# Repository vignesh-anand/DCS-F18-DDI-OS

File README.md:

# Open Source F18 DDI for DCS

Quick project to build a functional Digital Display Indicator for the F18 Hornet in DCS World. The project is not meant to be a replica of the real device but act as a completely functional module to enhance the immersion and combat experience. This might also be good for other modules like the F16 but this is untested Here's a demo:

[https://youtu.be/Hzj8HVoCLto](https://youtu.be/Hzj8HVoCLto)

### Bill of Materials

| Item Name | Price | Quantity | Purchase Link | Notes |
| --- | --- | --- | --- | --- |
| Custom PCB | $32 for 5 | 1 | [https://jlcpcb.com/](https://jlcpcb.com/) | Gerber files available in the repository, can order from any online PCB manufacturer. I like JLCPCB |
| Panasonic ESE-20D443 Switches | $1.18 | 20 | [https://www.digikey.com/en/products/detail/panasonic-electronic-components/ESE-20D443/593515](https://www.digikey.com/en/products/detail/panasonic-electronic-components/ESE-20D443/593515) | Available on Digikey or Mouser |
| Waveshare 4inch HDMI Capacitive Touch IPS LCD | $66 | 1 | [https://www.waveshare.com/4inch-hdmi-lcd-c.htm](https://www.waveshare.com/4inch-hdmi-lcd-c.htm) | Quicker shipping on Amazon but more expensive |
| Seed Studio Xiao Samd21 | $5.4 | 1 | [https://www.seeedstudio.com/Seeeduino-XIAO-Arduino-Microcontroller-SAMD21-Cortex-M0+-p-4426.html?srsltid=AfmBOoq5dJ23LE_dqcqwzZtpAwAl_5tHTdahaePdUQaOJm6XNmBkNnsp](https://www.seeedstudio.com/Seeeduino-XIAO-Arduino-Microcontroller-SAMD21-Cortex-M0+-p-4426.html?srsltid=AfmBOoq5dJ23LE_dqcqwzZtpAwAl_5tHTdahaePdUQaOJm6XNmBkNnsp) |  |
| M3 Bolts | $7.99 | 1 | [https://a.co/d/crp1qAX](https://a.co/d/crp1qAX) |  |
| M2.5 Bolts | $7.57 | 1 | [https://a.co/d/fGeQGS1](https://a.co/d/fGeQGS1) |  |

Total: $142 for one, $108 each for three

### Assembling the Module

**Step 1:** Solder header pins of the Seed Studio Xiao to the PCB and then solder on the board itself. A small dot on the PCB marks pin 1 of the board

**Step 2:** Solder the 20 push switches on the PCB

**Step 3:** Flash the Xiao board (see below)

**Step 4:** Mount the Display into the backplate using the M2.5 bolts

**Step 5:** Place the PCB in the backplate, place the front plate on it, and then secure all three using the M3 bolts

### Flashing the Microcontroller on Arduino IDE

**Step 1:** Download Arduino IDE - [https://www.arduino.cc/en/software/](https://www.arduino.cc/en/software/)

**Step 2:** Open the attached sketch in the IDE

**Step 3:** Add Seed studio board to the IDE - [https://wiki.seeedstudio.com/Seeed_Arduino_Boards/](https://wiki.seeedstudio.com/Seeed_Arduino_Boards/)

**Step 4:** In the library manager install the **HID-Project** library by NicoHood

**Step 5:** Set the Xiao to bootloader mode

**Step 6:** Under Tools → USB Stack, choose Arduino or Native

**Step 7:** Hit upload

**Step 8:** Disconnect and reconnect the microcontroller for it to appear as a joystick/controller

**Note:** If it does not appear as a joystick, find the device in device manager, and uninstall driver, then reconnect the device.

### Configuring DCS

**Exporting Displays:**

Exporting specific displays can be achieved via creating lua files: [https://wiki.hoggitworld.com/view/Exporting_MFCD_Displays](https://wiki.hoggitworld.com/view/Exporting_MFCD_Displays). Sample Lua for this DDI is attached to the repo. First set up your displays in windows as the following before continuing. Adjust the resolution in the lua file to match your resolution.

**Button Mappings:**

The DDI will detect like a regular gamepad/controller with 20 buttons. In the F18 DCS module, button one of the DDI is the bottom most button of the left bank. Choose the command in DCS then click the appropriate button on the module to map.

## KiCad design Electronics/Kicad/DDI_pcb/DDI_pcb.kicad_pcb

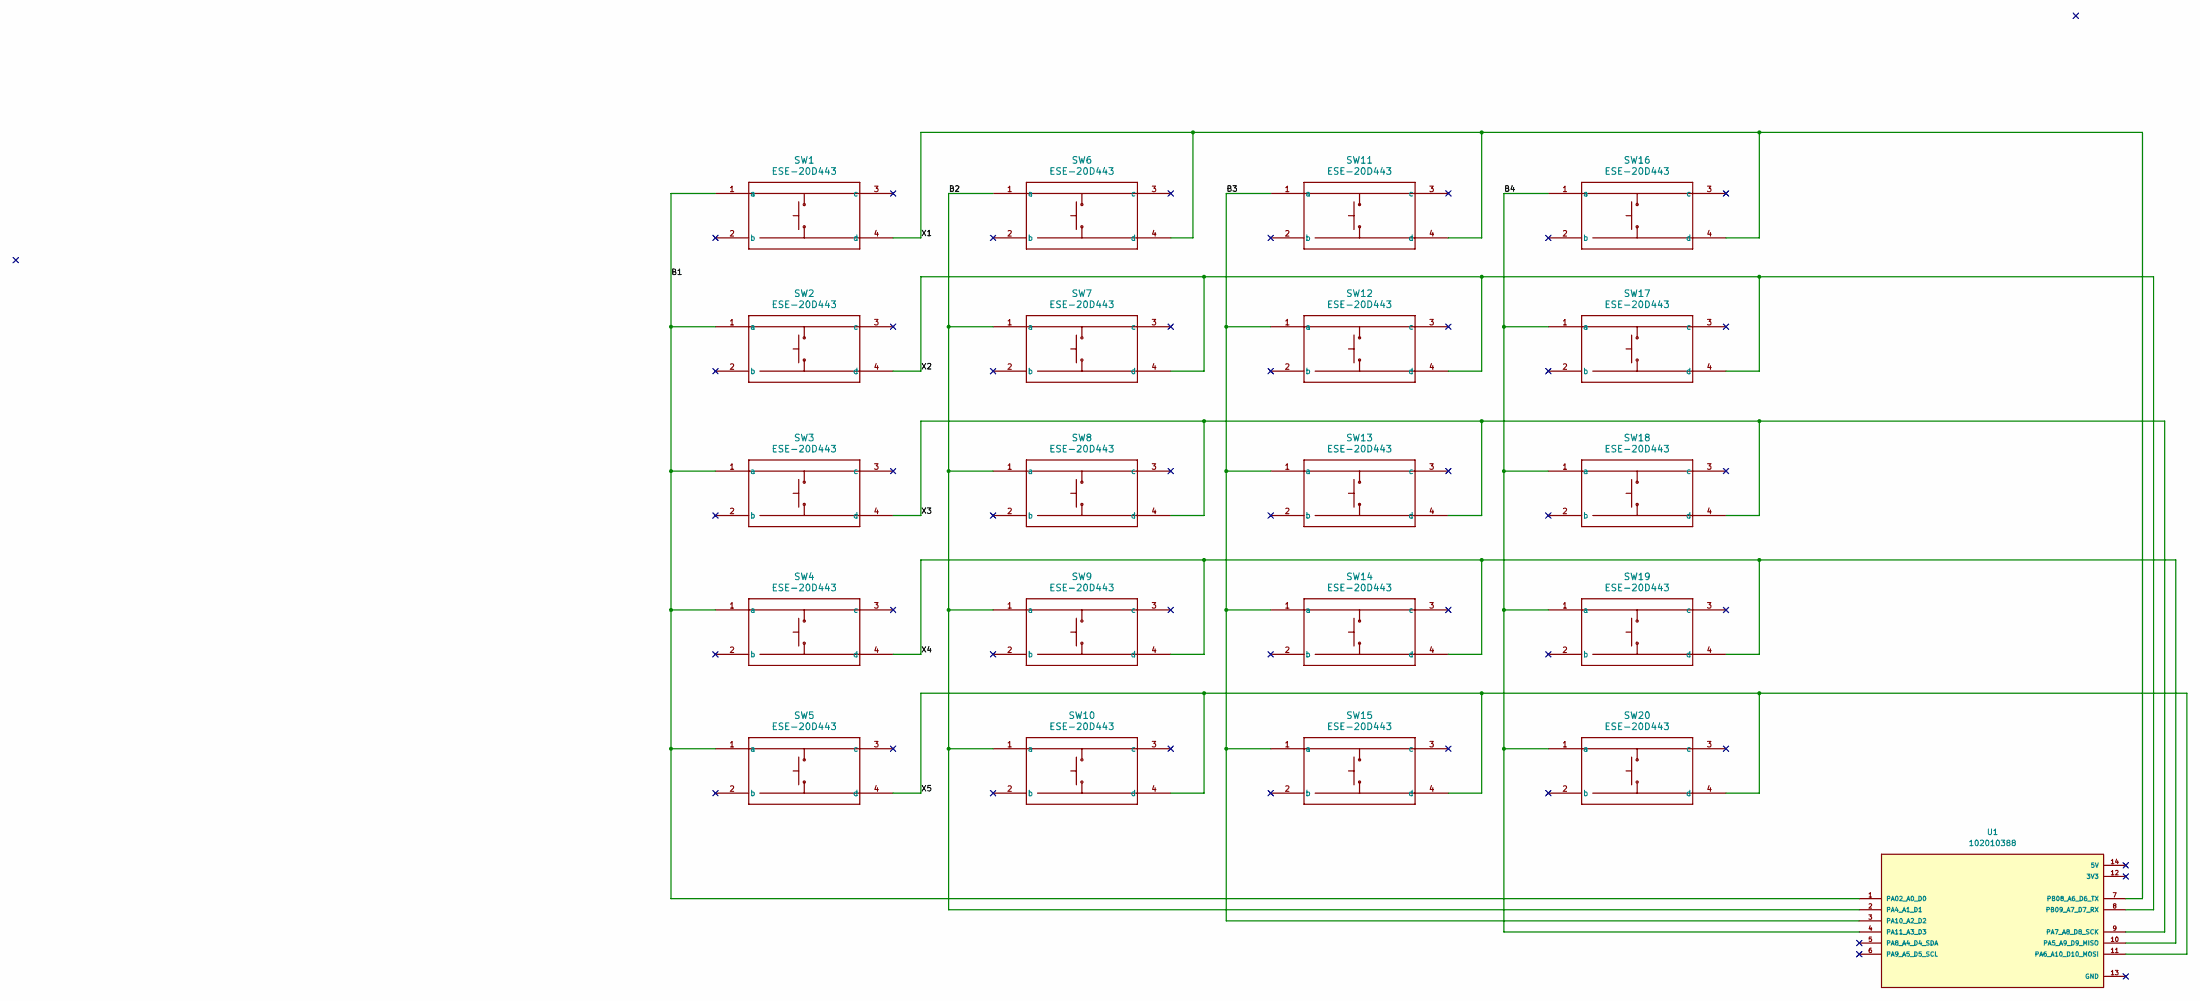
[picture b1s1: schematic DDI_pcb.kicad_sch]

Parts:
SW1, SW2, SW3, SW4, SW5, SW6, SW7, SW8, SW9, SW10, SW11, SW12, SW13, SW14, SW15, SW16, SW17, SW18, SW19, SW20: ESE-20D443; SW4_ESE-20D443_PAN
U1: 102010388; MODULE_113991054; PARTREV N/A

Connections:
/B1: SW1.1 (a), SW2.1 (a), SW3.1 (a), SW4.1 (a), SW5.1 (a), U1.1 (PA02_A0_D0)
/B2: SW6.1 (a), SW7.1 (a), SW8.1 (a), SW9.1 (a), SW10.1 (a), U1.2 (PA4_A1_D1)
/B3: SW11.1 (a), SW12.1 (a), SW13.1 (a), SW14.1 (a), SW15.1 (a), U1.3 (PA10_A2_D2)
/B4: SW16.1 (a), SW17.1 (a), SW18.1 (a), SW19.1 (a), SW20.1 (a), U1.4 (PA11_A3_D3)
/X1: SW1.4 (d), SW6.4 (d), SW11.4 (d), SW16.4 (d), U1.7 (PB08_A6_D6_TX)
/X2: SW2.4 (d), SW7.4 (d), SW12.4 (d), SW17.4 (d), U1.8 (PB09_A7_D7_RX)
/X3: SW3.4 (d), SW8.4 (d), SW13.4 (d), SW18.4 (d), U1.9 (PA7_A8_D8_SCK)
/X4: SW4.4 (d), SW9.4 (d), SW14.4 (d), SW19.4 (d), U1.10 (PA5_A9_D9_MISO)
/X5: SW5.4 (d), SW10.4 (d), SW15.4 (d), SW20.4 (d), U1.11 (PA6_A10_D10_MOSI)

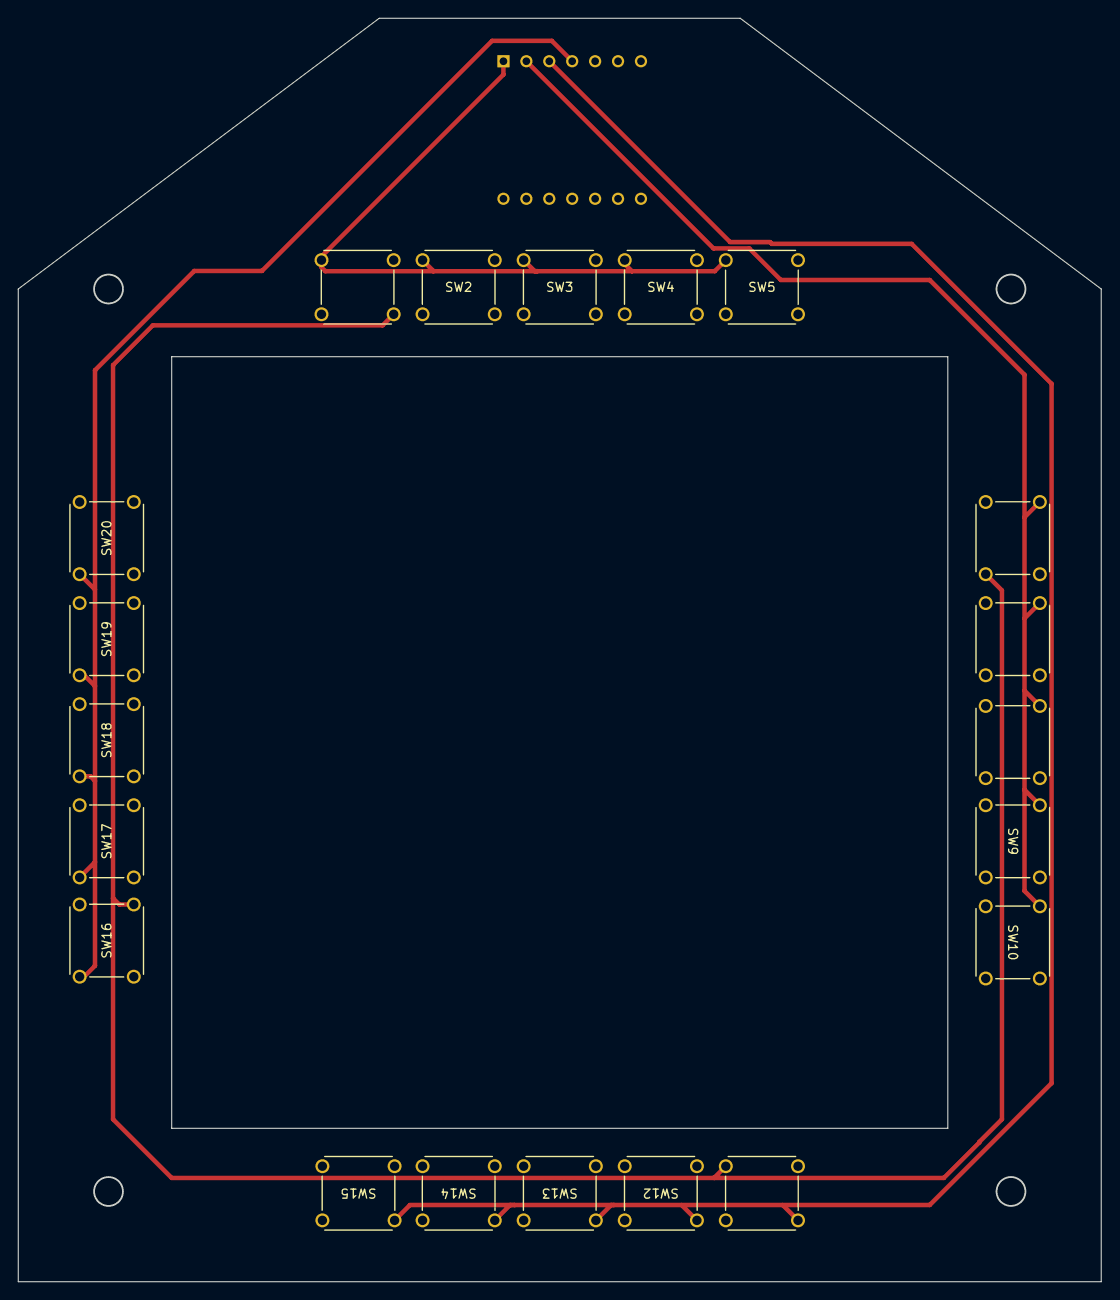
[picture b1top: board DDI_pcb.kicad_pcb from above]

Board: 4 copper layers, 120.0 x 140.0 mm, 21 parts (1 on the bottom side), 9 nets.

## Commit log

2025-07-06 Kicad Files
2025-07-06 gerbers and mechanical and videos
2025-07-06 readme available
2025-07-06 fixing readme
2025-07-06 updated price
